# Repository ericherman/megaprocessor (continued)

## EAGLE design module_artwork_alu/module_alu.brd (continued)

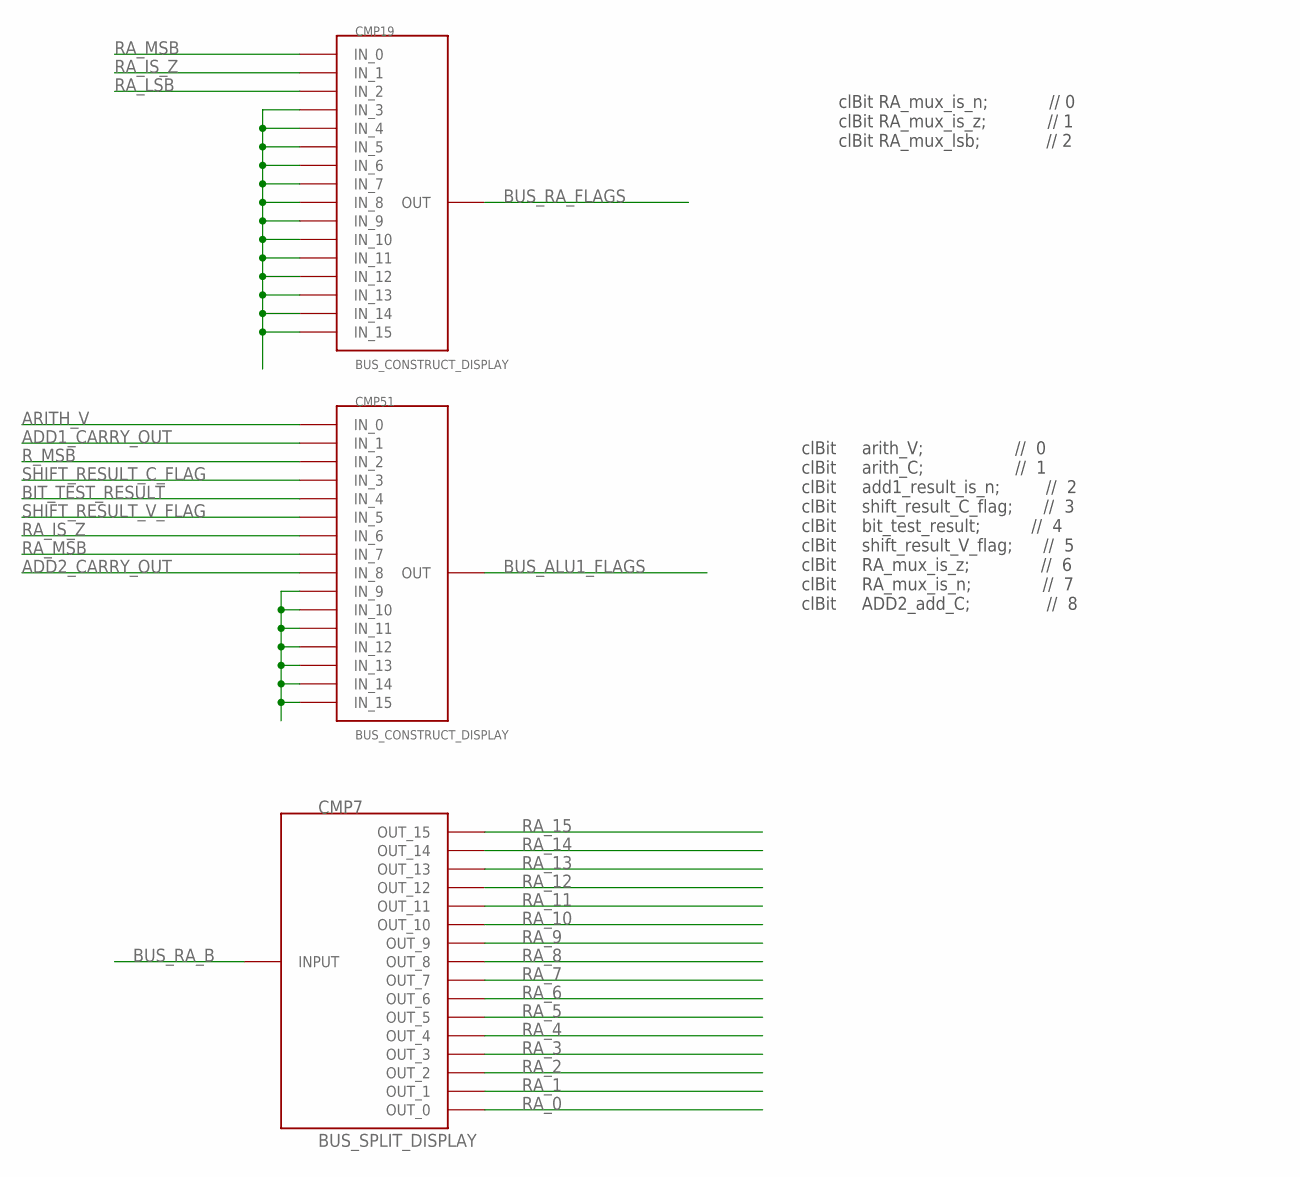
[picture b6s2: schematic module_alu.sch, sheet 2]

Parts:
CMP7: BUS_SPLIT_DISPLAY
CMP19, CMP51: BUS_CONSTRUCT_DISPLAY; BUS_SPLIT_DISPLAY

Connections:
ADD1_CARRY_OUT: CMP51.P$2 (IN_1); also elsewhere on the board
ADD2_CARRY_OUT: CMP51.P$9 (IN_8); also elsewhere on the board
ARITH_V: CMP51.P$1 (IN_0); also elsewhere on the board
BIT_TEST_RESULT: CMP51.P$5 (IN_4); also elsewhere on the board
BUS_ALU1_FLAGS: CMP51.INPUT (OUT)
BUS_RA_B: CMP7.INPUT; also elsewhere on the board
BUS_RA_FLAGS: CMP19.INPUT (OUT)
unnamed: CMP19.P$4 (IN_3), CMP19.P$5 (IN_4), CMP19.P$6 (IN_5), CMP19.P$7 (IN_6), CMP19.P$8 (IN_7), CMP19.P$9 (IN_8), CMP19.P$10 (IN_9), CMP19.P$11 (IN_10), CMP19.P$12 (IN_11), CMP19.P$13 (IN_12), CMP19.P$14 (IN_13), CMP19.P$15 (IN_14), CMP19.P$16 (IN_15)
unnamed: CMP51.P$10 (IN_9), CMP51.P$11 (IN_10), CMP51.P$12 (IN_11), CMP51.P$13 (IN_12), CMP51.P$14 (IN_13), CMP51.P$15 (IN_14), CMP51.P$16 (IN_15)
RA_0: CMP7.P$1 (OUT_0); also elsewhere on the board
RA_1: CMP7.P$2 (OUT_1); also elsewhere on the board
RA_2: CMP7.P$3 (OUT_2); also elsewhere on the board
RA_3: CMP7.P$4 (OUT_3); also elsewhere on the board
RA_4: CMP7.P$5 (OUT_4); also elsewhere on the board
RA_5: CMP7.P$6 (OUT_5); also elsewhere on the board
RA_6: CMP7.P$7 (OUT_6); also elsewhere on the board
RA_7: CMP7.P$8 (OUT_7); also elsewhere on the board
RA_8: CMP7.P$9 (OUT_8); also elsewhere on the board
RA_9: CMP7.P$10 (OUT_9); also elsewhere on the board
RA_10: CMP7.P$11 (OUT_10); also elsewhere on the board
RA_11: CMP7.P$12 (OUT_11); also elsewhere on the board
RA_12: CMP7.P$13 (OUT_12); also elsewhere on the board
RA_13: CMP7.P$14 (OUT_13); also elsewhere on the board
RA_14: CMP7.P$15 (OUT_14); also elsewhere on the board
RA_15: CMP7.P$16 (OUT_15); also elsewhere on the board
RA_IS_Z: CMP19.P$2 (IN_1), CMP51.P$7 (IN_6); also elsewhere on the board
RA_LSB: CMP19.P$3 (IN_2); also elsewhere on the board
RA_MSB: CMP19.P$1 (IN_0), CMP51.P$8 (IN_7); also elsewhere on the board
R_MSB: CMP51.P$3 (IN_2); also elsewhere on the board
SHIFT_RESULT_C_FLAG: CMP51.P$4 (IN_3); also elsewhere on the board
SHIFT_RESULT_V_FLAG: CMP51.P$6 (IN_5); also elsewhere on the board

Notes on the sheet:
clBit RA_mux_is_n; // 0 clBit RA_mux_is_z; // 1 clBit RA_mux_lsb; // 2
clBit arith_V; // 0 clBit arith_C; // 1 clBit add1_result_is_n; // 2 clBit shift_result_C_flag; // 3 clBit bit_test_result; // 4 clBit shift_result_V_flag; // 5 clBit RA_mux_is_z; // 6 clBit RA_mux_is_n; // 7 clBit ADD2_add_C; // 8

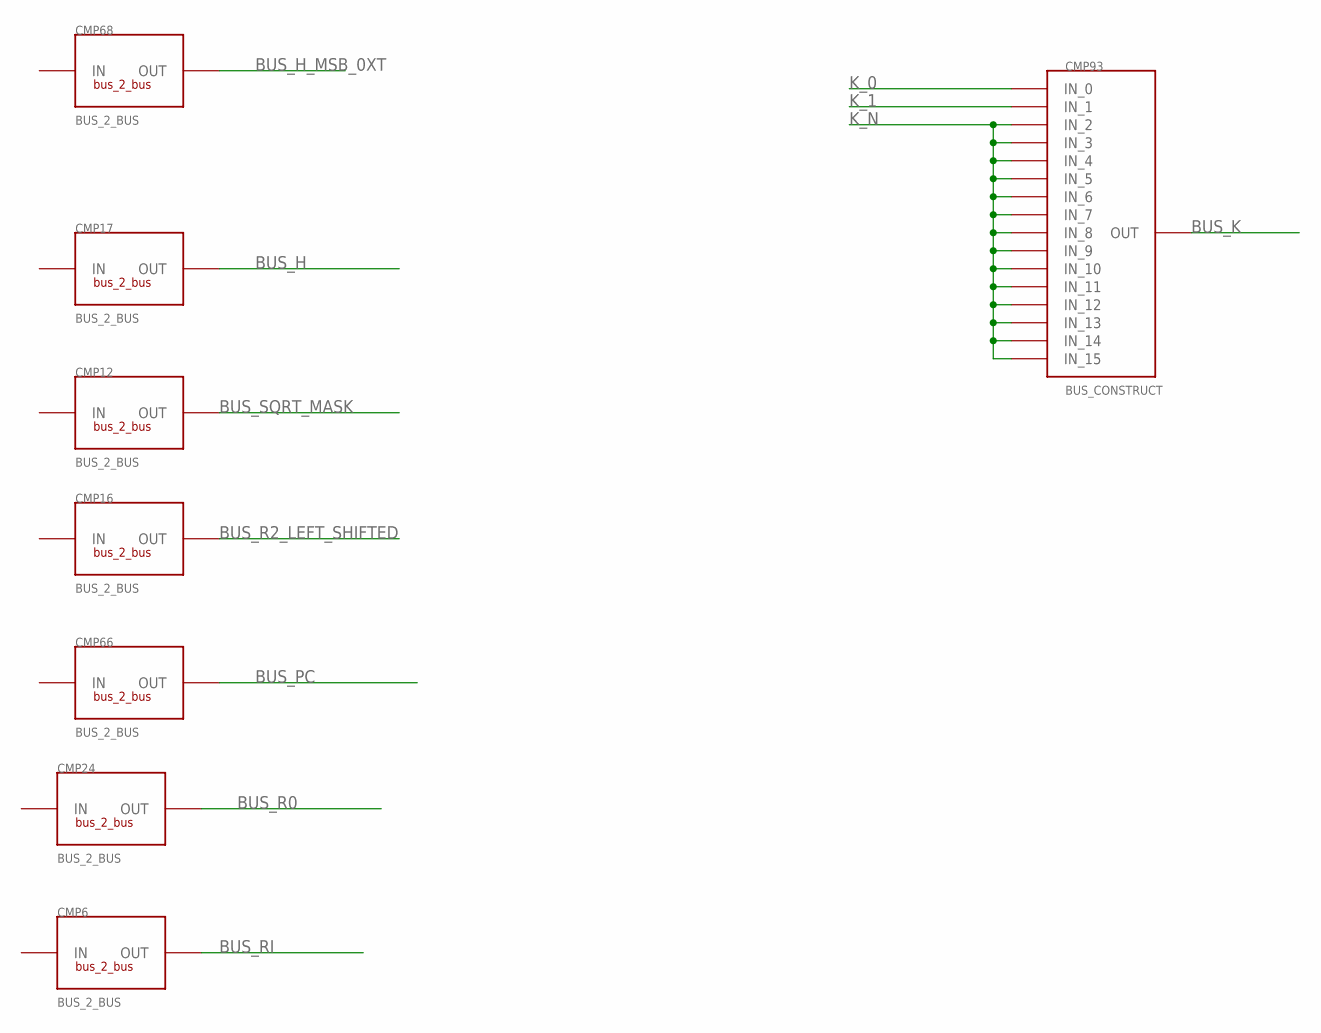
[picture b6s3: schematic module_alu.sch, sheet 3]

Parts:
CMP6, CMP12, CMP16, CMP17, CMP24, CMP66, CMP68: BUS_2_BUS; BUS2BUS
CMP93: BUS_CONSTRUCT; BUS_SPLIT

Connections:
BUS_H: CMP17.P$2 (OUT); also elsewhere on the board
BUS_H_MSB_0XT: CMP68.P$2 (OUT); also elsewhere on the board
BUS_K: CMP93.INPUT (OUT); also elsewhere on the board
BUS_PC: CMP66.P$2 (OUT); also elsewhere on the board
BUS_R0: CMP24.P$2 (OUT); also elsewhere on the board
BUS_R2_LEFT_SHIFTED: CMP16.P$2 (OUT); also elsewhere on the board
BUS_RI: CMP6.P$2 (OUT); also elsewhere on the board
BUS_SQRT_MASK: CMP12.P$2 (OUT); also elsewhere on the board
K_0: CMP93.P$1 (IN_0); also elsewhere on the board
K_1: CMP93.P$2 (IN_1); also elsewhere on the board
K_N: CMP93.P$3 (IN_2), CMP93.P$4 (IN_3), CMP93.P$5 (IN_4), CMP93.P$6 (IN_5), CMP93.P$7 (IN_6), CMP93.P$8 (IN_7), CMP93.P$9 (IN_8), CMP93.P$10 (IN_9), CMP93.P$11 (IN_10), CMP93.P$12 (IN_11), CMP93.P$13 (IN_12), CMP93.P$14 (IN_13), CMP93.P$15 (IN_14), CMP93.P$16 (IN_15); also elsewhere on the board

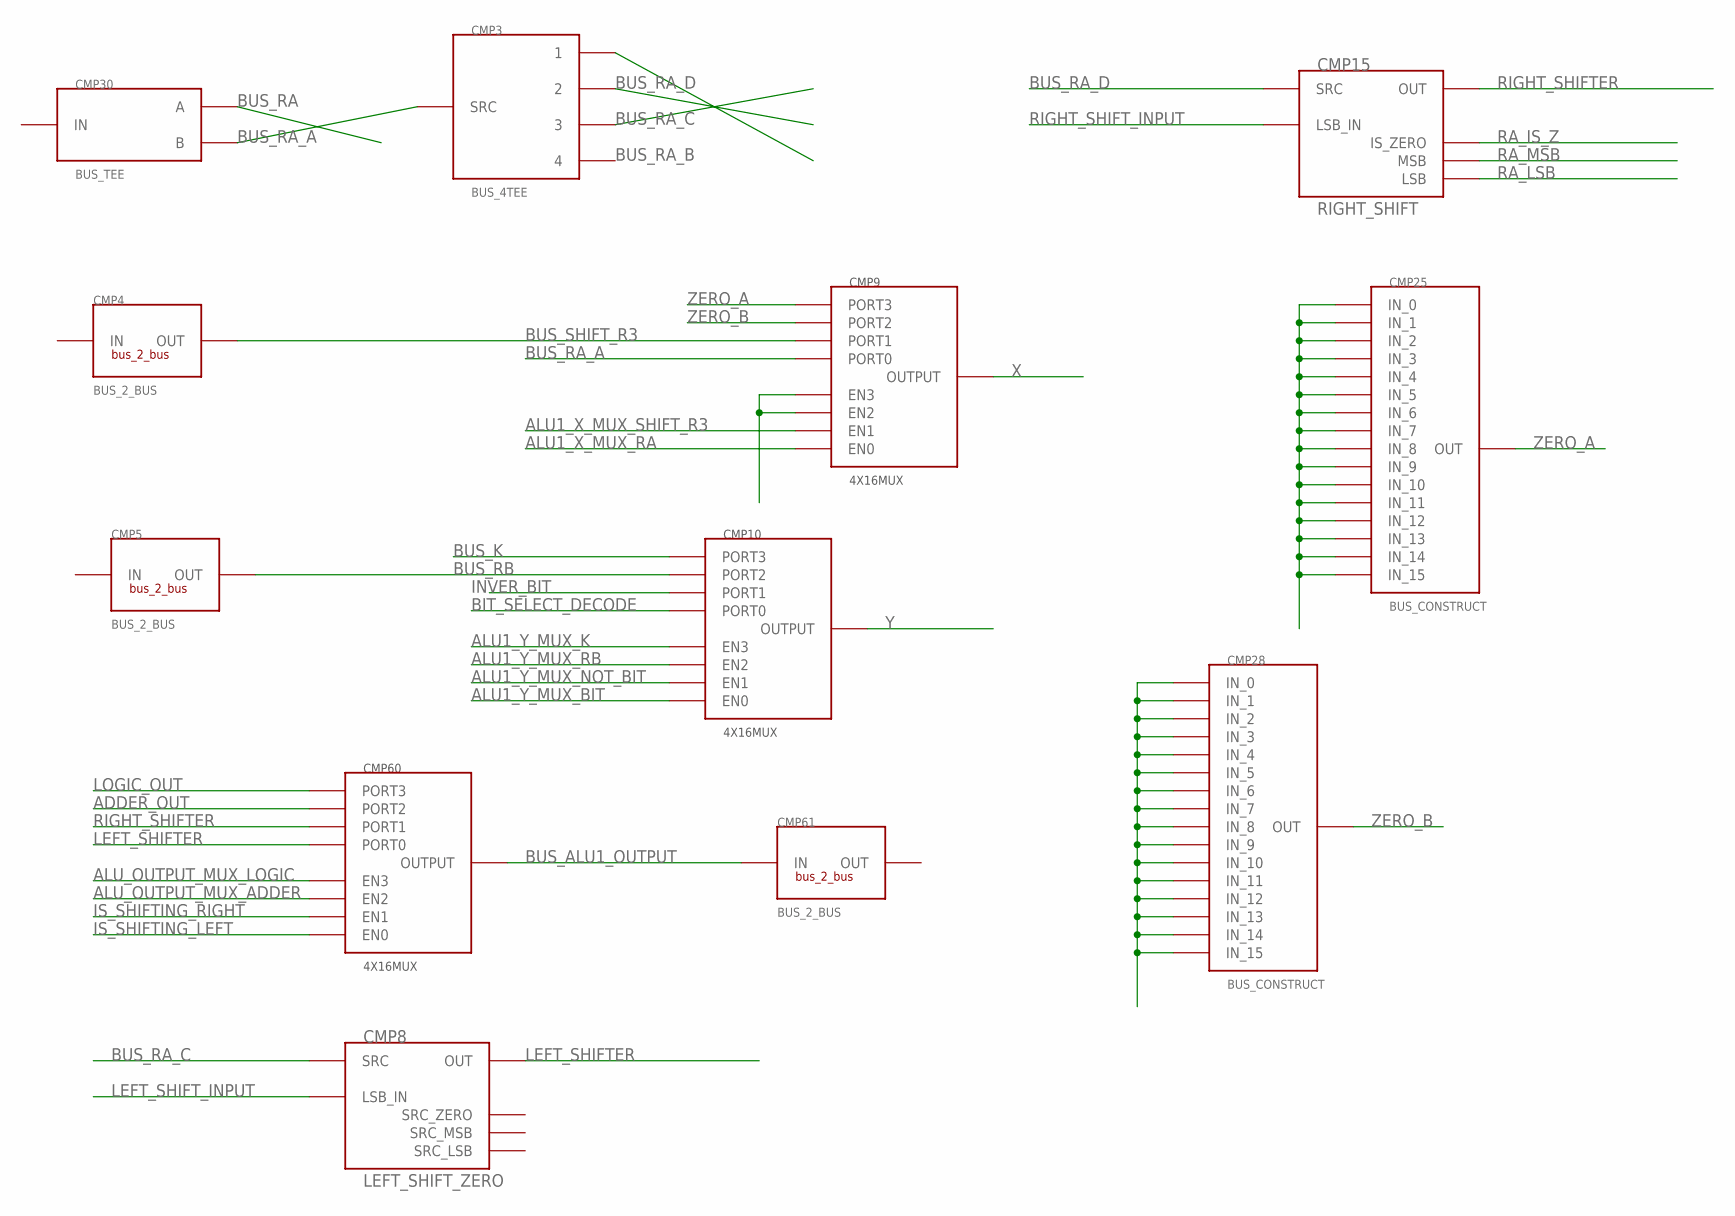
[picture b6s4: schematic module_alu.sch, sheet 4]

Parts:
CMP3: BUS_4TEE
CMP4, CMP5, CMP61: BUS_2_BUS; BUS2BUS
CMP8: LEFT_SHIFT_ZERO; SHIFT_ZERO
CMP9, CMP10, CMP60: 4X16MUX
CMP15: RIGHT_SHIFT; SHIFT_ZERO
CMP25, CMP28: BUS_CONSTRUCT; BUS_SPLIT
CMP30: BUS_TEE

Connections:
ADDER_OUT: CMP60.PORT2; also elsewhere on the board
ALU1_X_MUX_RA: CMP9.EN0; also elsewhere on the board
ALU1_X_MUX_SHIFT_R3: CMP9.EN1; also elsewhere on the board
ALU1_Y_MUX_BIT: CMP10.EN0; also elsewhere on the board
ALU1_Y_MUX_K: CMP10.EN3; also elsewhere on the board
ALU1_Y_MUX_NOT_BIT: CMP10.EN1; also elsewhere on the board
ALU1_Y_MUX_RB: CMP10.EN2; also elsewhere on the board
ALU_OUTPUT_MUX_ADDER: CMP60.EN2; also elsewhere on the board
ALU_OUTPUT_MUX_LOGIC: CMP60.EN3; also elsewhere on the board
BIT_SELECT_DECODE: CMP10.PORT0; also elsewhere on the board
BUS_ALU1_OUTPUT: CMP60.PORTOUT (OUTPUT), CMP61.P$1 (IN)
BUS_K: CMP10.PORT3; also elsewhere on the board
BUS_RA: CMP3.SRC, CMP30.OUTB (B)
BUS_RA_A: CMP9.PORT0, CMP30.OUT_A (A)
BUS_RA_B: CMP3.1; also elsewhere on the board
BUS_RA_C: CMP3.2, CMP8.LSRC (SRC)
BUS_RA_D: CMP3.3, CMP15.RSRC (SRC)
BUS_RB: CMP5.P$2 (OUT), CMP10.PORT2
BUS_SHIFT_R3: CMP4.P$2 (OUT), CMP9.PORT1
INVER_BIT: CMP10.PORT1; also elsewhere on the board
IS_SHIFTING_LEFT: CMP60.EN0; also elsewhere on the board
IS_SHIFTING_RIGHT: CMP60.EN1; also elsewhere on the board
LEFT_SHIFTER: CMP8.RSRC (OUT), CMP60.PORT0
LEFT_SHIFT_INPUT: CMP8.SHIFT_IN (LSB_IN); also elsewhere on the board
LOGIC_OUT: CMP60.PORT3; also elsewhere on the board
unnamed: CMP9.EN2, CMP9.EN3
unnamed: CMP25.P$1 (IN_0), CMP25.P$2 (IN_1), CMP25.P$3 (IN_2), CMP25.P$4 (IN_3), CMP25.P$5 (IN_4), CMP25.P$6 (IN_5), CMP25.P$7 (IN_6), CMP25.P$8 (IN_7), CMP25.P$9 (IN_8), CMP25.P$10 (IN_9), CMP25.P$11 (IN_10), CMP25.P$12 (IN_11), CMP25.P$13 (IN_12), CMP25.P$14 (IN_13), CMP25.P$15 (IN_14), CMP25.P$16 (IN_15)
unnamed: CMP28.P$1 (IN_0), CMP28.P$2 (IN_1), CMP28.P$3 (IN_2), CMP28.P$4 (IN_3), CMP28.P$5 (IN_4), CMP28.P$6 (IN_5), CMP28.P$7 (IN_6), CMP28.P$8 (IN_7), CMP28.P$9 (IN_8), CMP28.P$10 (IN_9), CMP28.P$11 (IN_10), CMP28.P$12 (IN_11), CMP28.P$13 (IN_12), CMP28.P$14 (IN_13), CMP28.P$15 (IN_14), CMP28.P$16 (IN_15)
RA_IS_Z: CMP15.IS_ZERO; also elsewhere on the board
RA_LSB: CMP15.LSB; also elsewhere on the board
RA_MSB: CMP15.MSB; also elsewhere on the board
RIGHT_SHIFTER: CMP15.LSRC (OUT), CMP60.PORT1
RIGHT_SHIFT_INPUT: CMP15.SHIFT_IN (LSB_IN); also elsewhere on the board
X: CMP9.PORTOUT (OUTPUT); also elsewhere on the board
Y: CMP10.PORTOUT (OUTPUT); also elsewhere on the board
ZERO_A: CMP9.PORT3, CMP25.INPUT (OUT)
ZERO_B: CMP9.PORT2, CMP28.INPUT (OUT)

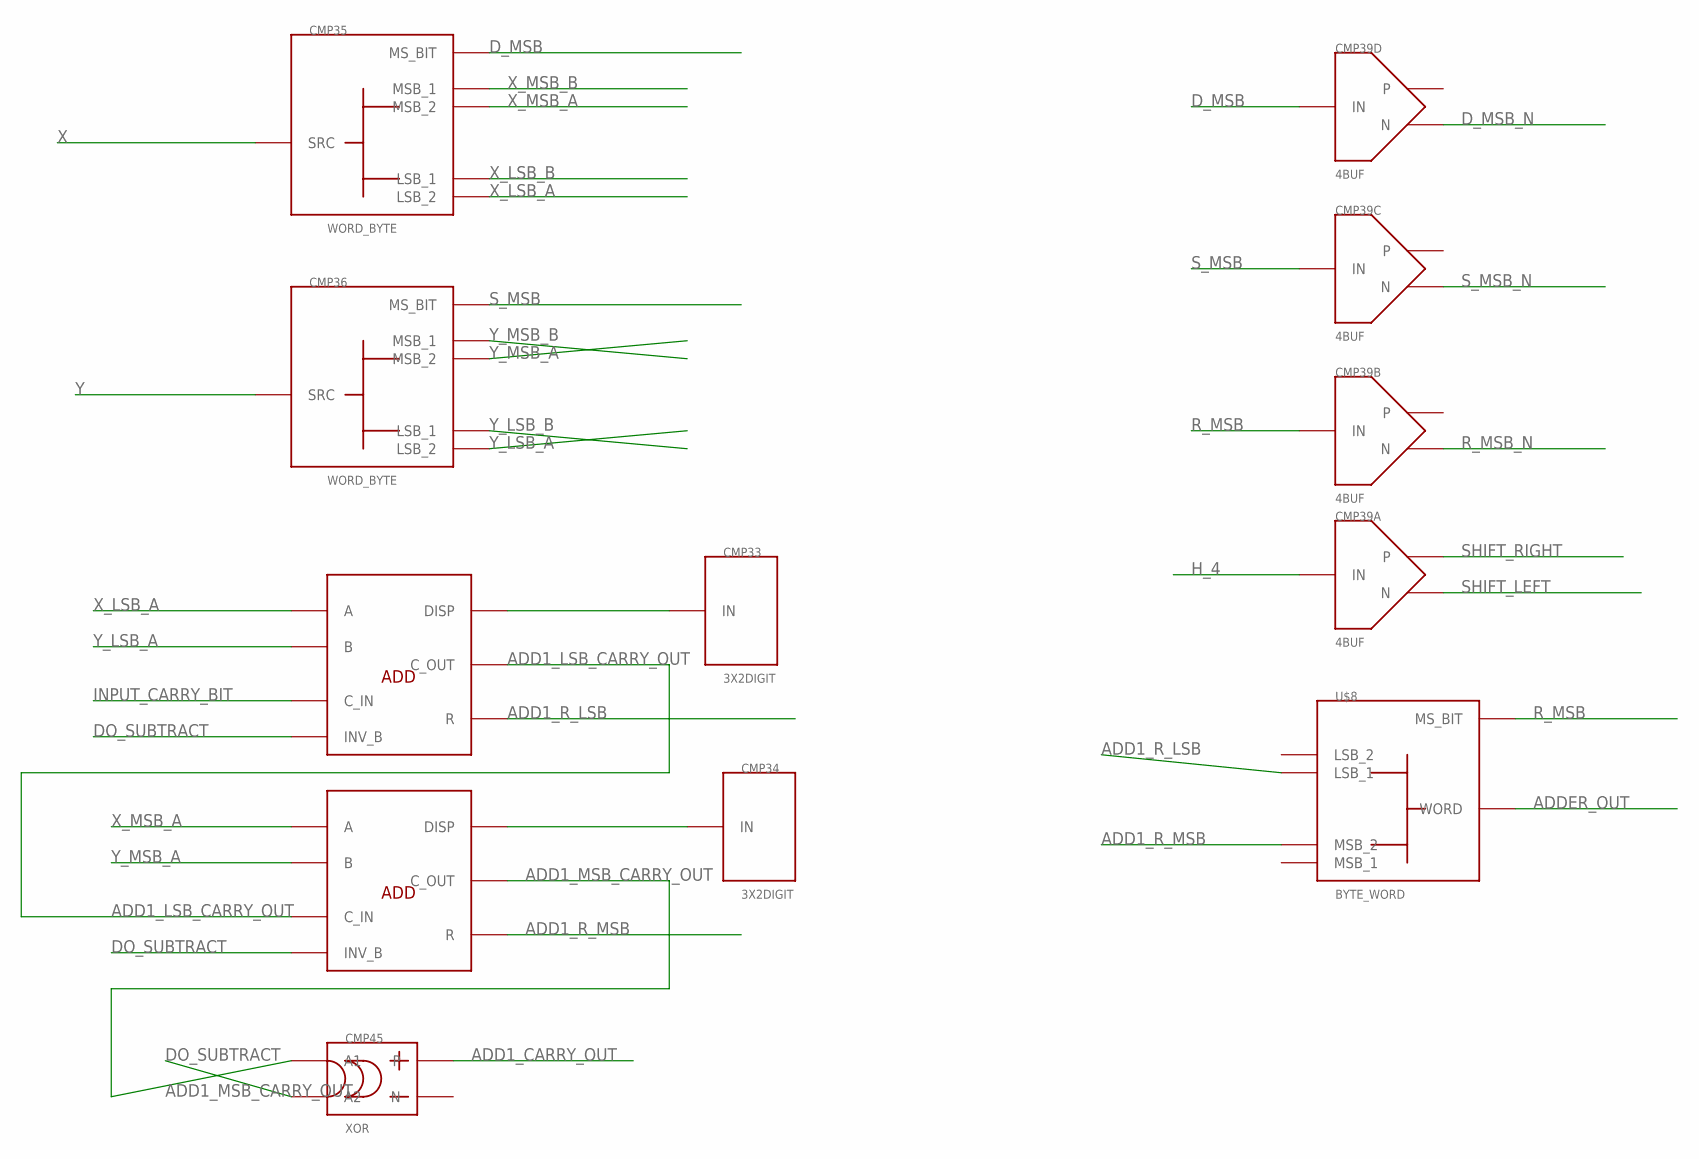
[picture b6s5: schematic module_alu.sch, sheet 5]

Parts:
CMP31, CMP32: 8BIT_ADD_SUB
CMP33, CMP34: 3X2DIGIT
CMP35, CMP36: WORD_BYTE
CMP39: 4BUF
CMP45: XOR
U$8: BYTE_WORD; WORD_BYTE

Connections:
ADD1_CARRY_OUT: CMP45.OUT_P; also elsewhere on the board
ADD1_LSB_CARRY_OUT: CMP31.C_OUT, CMP32.C_IN
ADD1_MSB_CARRY_OUT: CMP32.C_OUT, CMP45.P$1 (A1)
ADD1_R_LSB: CMP31.R, U$8.LSB_1
ADD1_R_MSB: CMP32.R, U$8.MSB_2
ADDER_OUT: U$8.SRC (WORD); also elsewhere on the board
DO_SUBTRACT: CMP31.INV_B, CMP32.INV_B, CMP45.P$2 (A2); also elsewhere on the board
D_MSB: CMP35.MS_BIT, CMP39.A4 (IN); also elsewhere on the board
D_MSB_N: CMP39.N4 (N); also elsewhere on the board
H_4: CMP39.A1 (IN); also elsewhere on the board
INPUT_CARRY_BIT: CMP31.C_IN; also elsewhere on the board
unnamed: CMP31.DISP, CMP33.P$1
unnamed: CMP32.DISP, CMP34.P$1
R_MSB: CMP39.A2 (IN), U$8.MS_BIT; also elsewhere on the board
R_MSB_N: CMP39.N2 (N); also elsewhere on the board
SHIFT_LEFT: CMP39.N1 (N); also elsewhere on the board
SHIFT_RIGHT: CMP39.P1; also elsewhere on the board
S_MSB: CMP36.MS_BIT, CMP39.A3 (IN); also elsewhere on the board
S_MSB_N: CMP39.N3 (N); also elsewhere on the board
X: CMP35.SRC; also elsewhere on the board
X_LSB_A: CMP31.A, CMP35.LSB_2
X_LSB_B: CMP35.LSB_1; also elsewhere on the board
X_MSB_A: CMP32.A, CMP35.MSB_2
X_MSB_B: CMP35.MSB_1; also elsewhere on the board
Y: CMP36.SRC; also elsewhere on the board
Y_LSB_A: CMP31.B, CMP36.LSB_1
Y_LSB_B: CMP36.LSB_2; also elsewhere on the board
Y_MSB_A: CMP32.B, CMP36.MSB_1
Y_MSB_B: CMP36.MSB_2; also elsewhere on the board

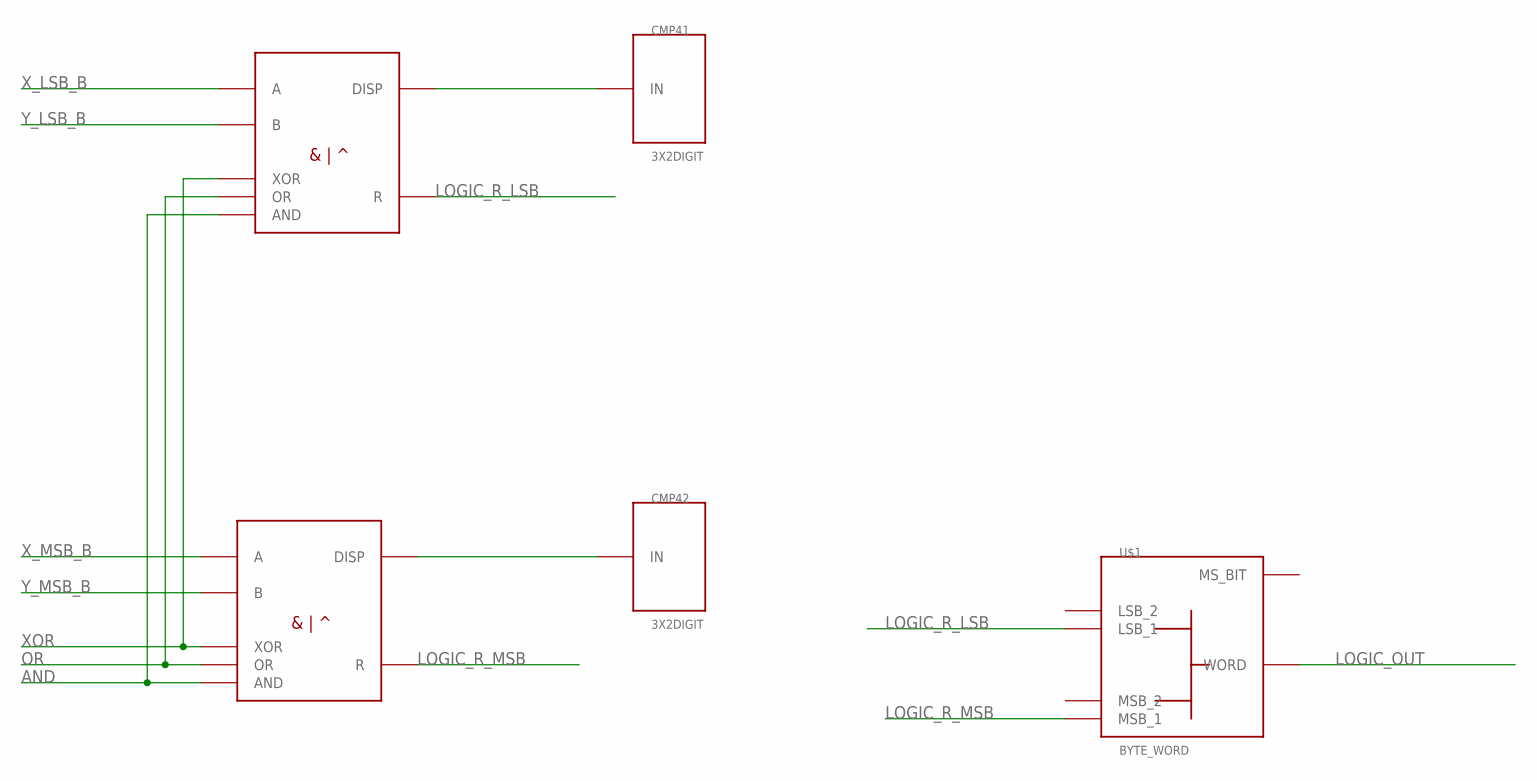
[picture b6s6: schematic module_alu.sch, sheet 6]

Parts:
CMP41, CMP42: 3X2DIGIT
CMP46, CMP47: 8BIT_LOGIC
U$1: BYTE_WORD; WORD_BYTE

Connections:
AND: CMP46.AND, CMP47.AND; also elsewhere on the board
LOGIC_OUT: U$1.SRC (WORD); also elsewhere on the board
LOGIC_R_LSB: CMP47.R, U$1.LSB_1
LOGIC_R_MSB: CMP46.R, U$1.MSB_1
unnamed: CMP41.P$1, CMP47.DISP
unnamed: CMP42.P$1, CMP46.DISP
OR: CMP46.OR, CMP47.OR; also elsewhere on the board
XOR: CMP46.XOR, CMP47.XOR; also elsewhere on the board
X_LSB_B: CMP47.A; also elsewhere on the board
X_MSB_B: CMP46.A; also elsewhere on the board
Y_LSB_B: CMP47.B; also elsewhere on the board
Y_MSB_B: CMP46.B; also elsewhere on the board

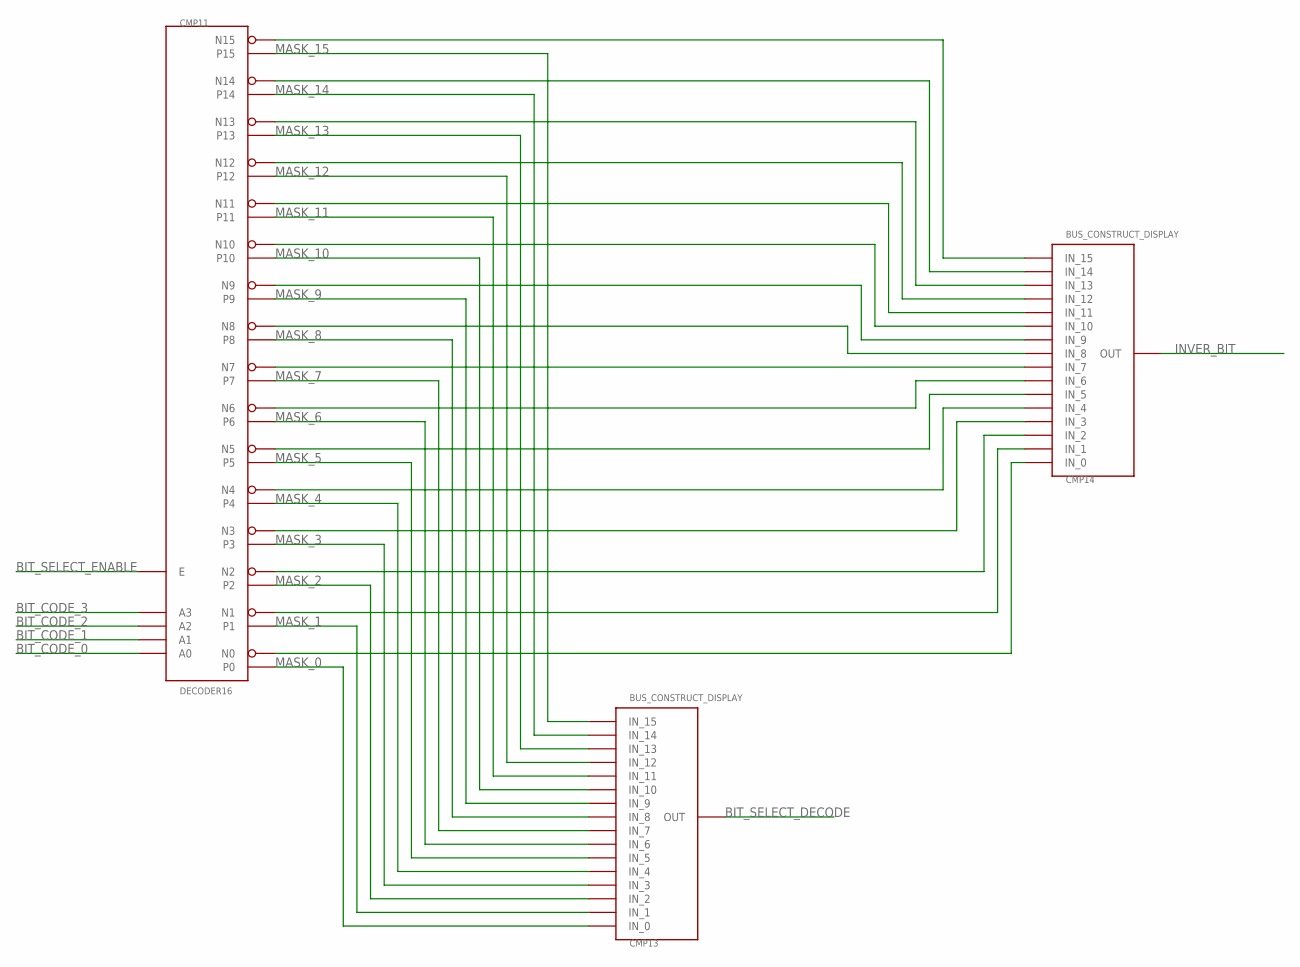
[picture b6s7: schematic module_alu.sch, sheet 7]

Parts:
CMP11: DECODER16
CMP13, CMP14: BUS_CONSTRUCT_DISPLAY; BUS_SPLIT_DISPLAY

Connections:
BIT_CODE_0: CMP11.A0; also elsewhere on the board
BIT_CODE_1: CMP11.A1; also elsewhere on the board
BIT_CODE_2: CMP11.A2; also elsewhere on the board
BIT_CODE_3: CMP11.A3; also elsewhere on the board
BIT_SELECT_DECODE: CMP13.INPUT (OUT); also elsewhere on the board
BIT_SELECT_ENABLE: CMP11.E; also elsewhere on the board
INVER_BIT: CMP14.INPUT (OUT); also elsewhere on the board
MASK_0: CMP11.P0, CMP13.P$1 (IN_0); also elsewhere on the board
MASK_1: CMP11.P1, CMP13.P$2 (IN_1); also elsewhere on the board
MASK_2: CMP11.P2, CMP13.P$3 (IN_2); also elsewhere on the board
MASK_3: CMP11.P3, CMP13.P$4 (IN_3); also elsewhere on the board
MASK_4: CMP11.P4, CMP13.P$5 (IN_4); also elsewhere on the board
MASK_5: CMP11.P5, CMP13.P$6 (IN_5); also elsewhere on the board
MASK_6: CMP11.P6, CMP13.P$7 (IN_6); also elsewhere on the board
MASK_7: CMP11.P7, CMP13.P$8 (IN_7); also elsewhere on the board
MASK_8: CMP11.P8, CMP13.P$9 (IN_8); also elsewhere on the board
MASK_9: CMP11.P9, CMP13.P$10 (IN_9); also elsewhere on the board
MASK_10: CMP11.P10, CMP13.P$11 (IN_10); also elsewhere on the board
MASK_11: CMP11.P11, CMP13.P$12 (IN_11); also elsewhere on the board
MASK_12: CMP11.P12, CMP13.P$13 (IN_12); also elsewhere on the board
MASK_13: CMP11.P13, CMP13.P$14 (IN_13); also elsewhere on the board
MASK_14: CMP11.P14, CMP13.P$15 (IN_14); also elsewhere on the board
MASK_15: CMP11.P15, CMP13.P$16 (IN_15); also elsewhere on the board
unnamed: CMP11.N0, CMP14.P$1 (IN_0)
unnamed: CMP11.N1, CMP14.P$2 (IN_1)
unnamed: CMP11.N2, CMP14.P$3 (IN_2)
unnamed: CMP11.N3, CMP14.P$4 (IN_3)
unnamed: CMP11.N4, CMP14.P$5 (IN_4)
unnamed: CMP11.N5, CMP14.P$6 (IN_5)
unnamed: CMP11.N6, CMP14.P$7 (IN_6)
unnamed: CMP11.N7, CMP14.P$8 (IN_7)
unnamed: CMP11.N8, CMP14.P$9 (IN_8)
unnamed: CMP11.N9, CMP14.P$10 (IN_9)
unnamed: CMP11.N10, CMP14.P$11 (IN_10)
unnamed: CMP11.N11, CMP14.P$12 (IN_11)
unnamed: CMP11.N12, CMP14.P$13 (IN_12)
unnamed: CMP11.N13, CMP14.P$14 (IN_13)
unnamed: CMP11.N14, CMP14.P$15 (IN_14)
unnamed: CMP11.N15, CMP14.P$16 (IN_15)

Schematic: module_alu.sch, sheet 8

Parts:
CMP48, CMP49: 2X3AND_OR
CMP50: 2AND
CMP52: 4X2AND_OR

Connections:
ARITH_ADD_V: CMP48.OUT_P, CMP52.P$8 (D1)
ARITH_NEG_V: CMP50.OUT_P, CMP52.P$4 (B1)
ARITH_SUB_V: CMP49.OUT_P, CMP52.P$6 (C1)
ARITH_V: CMP52.OUT_P; also elsewhere on the board
D_MSB: CMP48.P$4 (B0), CMP49.P$5 (B1); also elsewhere on the board
D_MSB_N: CMP48.P$3 (A2), CMP49.P$1 (A0); also elsewhere on the board
unnamed: CMP52.P$1 (A0), CMP52.P$2 (A1)
R_MSB: CMP48.P$2 (A1), CMP49.P$3 (A2), CMP50.P$2 (2); also elsewhere on the board
R_MSB_N: CMP48.P$5 (B1), CMP49.P$4 (B0); also elsewhere on the board
S_MSB: CMP48.P$6 (B2), CMP49.P$2 (A1), CMP50.P$1 (1); also elsewhere on the board
S_MSB_N: CMP48.P$1 (A0), CMP49.P$6 (B2); also elsewhere on the board
USE_ADD_V: CMP52.P$7 (D0); also elsewhere on the board
USE_NEG_V: CMP52.P$3 (B0); also elsewhere on the board
USE_SUB_V: CMP52.P$5 (C0); also elsewhere on the board

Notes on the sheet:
arith_add_V = Cpnt_2x3AND_OR( S_msb, D_msb, ~R_msb, ~S_msb, ~D_msb, R_msb);
arith_sub_V = Cpnt_2x3AND_OR(~S_msb, D_msb, ~R_msb, S_msb, ~D_msb, R_msb);
arith_neg_V = Cpnt_2AND(S_msb, R_msb);
arith_V = Cpnt_4x2AND_OR(arith_add_V,bus_alu1_operation_ctrl.use_add_V, arith_sub_V,bus_alu1_operation_ctrl.use_sub_V, arith_neg_V,bus_alu1_operation_ctrl.use_neg_V, BIT_VAL_0, BIT_VAL_0);

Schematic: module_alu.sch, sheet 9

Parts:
CMP53, CMP54: 8X2AND_OR
CMP55: 2OR

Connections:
BIT_TEST_RESULT: CMP55.OUT_M (N); also elsewhere on the board
MASK_0: CMP54.P$2 (A1); also elsewhere on the board
MASK_1: CMP54.P$4 (B1); also elsewhere on the board
MASK_2: CMP54.P$6 (C1); also elsewhere on the board
MASK_3: CMP54.P$8 (D1); also elsewhere on the board
MASK_4: CMP54.P$10 (E2); also elsewhere on the board
MASK_5: CMP54.P$12 (F2); also elsewhere on the board
MASK_6: CMP54.P$14 (G2); also elsewhere on the board
MASK_7: CMP54.P$16 (H2); also elsewhere on the board
MASK_8: CMP53.P$2 (A1); also elsewhere on the board
MASK_9: CMP53.P$4 (B1); also elsewhere on the board
MASK_10: CMP53.P$6 (C1); also elsewhere on the board
MASK_11: CMP53.P$8 (D1); also elsewhere on the board
MASK_12: CMP53.P$10 (E2); also elsewhere on the board
MASK_13: CMP53.P$12 (F2); also elsewhere on the board
MASK_14: CMP53.P$14 (G2); also elsewhere on the board
MASK_15: CMP53.P$16 (H2); also elsewhere on the board
unnamed: CMP53.OUT_P, CMP55.P$2 (A1)
unnamed: CMP54.OUT_P, CMP55.P$1 (A2)
RA_0: CMP54.P$1 (A0); also elsewhere on the board
RA_1: CMP54.P$3 (B0); also elsewhere on the board
RA_2: CMP54.P$5 (C0); also elsewhere on the board
RA_3: CMP54.P$7 (D0); also elsewhere on the board
RA_4: CMP54.P$9 (E1); also elsewhere on the board
RA_5: CMP54.P$11 (F1); also elsewhere on the board
RA_6: CMP54.P$13 (G1); also elsewhere on the board
RA_7: CMP54.P$15 (H1); also elsewhere on the board
RA_8: CMP53.P$1 (A0); also elsewhere on the board
RA_9: CMP53.P$3 (B0); also elsewhere on the board
RA_10: CMP53.P$5 (C0); also elsewhere on the board
RA_11: CMP53.P$7 (D0); also elsewhere on the board
RA_12: CMP53.P$9 (E1); also elsewhere on the board
RA_13: CMP53.P$11 (F1); also elsewhere on the board
RA_14: CMP53.P$13 (G1); also elsewhere on the board
RA_15: CMP53.P$15 (H1); also elsewhere on the board

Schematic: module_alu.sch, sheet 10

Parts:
CMP38: XOR
CMP56: 2X2AND_OR

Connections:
RA_14: CMP38.P$2 (A2); also elsewhere on the board
RA_LSB: CMP56.P$1 (A0); also elsewhere on the board
RA_MSB: CMP38.P$1 (A1), CMP56.P$3 (B0); also elsewhere on the board
SHIFT_LEFT: CMP56.P$4 (B1); also elsewhere on the board
SHIFT_RESULT_C_FLAG: CMP56.OUT_P; also elsewhere on the board
SHIFT_RESULT_V_FLAG: CMP38.OUT_P; also elsewhere on the board
SHIFT_RIGHT: CMP56.P$2 (A1); also elsewhere on the board

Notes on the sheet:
shift_result_C_flag = Cpnt_2x2AND_OR(~bus_alu1_operation_ctrl.H_4, bus_RA[15], bus_alu1_operation_ctrl.H_4, bus_RA[ 0]);
shift_result_V_flag = Cpnt_XOR( bus_RA[15], bus_RA[14] );

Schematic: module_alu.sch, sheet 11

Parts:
CMP70, CMP71: 4X16MUX
CMP72: BUS_CONSTRUCT; BUS_SPLIT

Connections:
ADD2_X: CMP70.PORTOUT (OUTPUT); also elsewhere on the board
ADD2_X_MUX_PC: CMP70.EN1; also elsewhere on the board
ADD2_X_MUX_RI: CMP70.EN3; also elsewhere on the board
ADD2_X_MUX_SHIFT_R2: CMP70.EN2; also elsewhere on the board
ADD2_X_MUX_SQRT_MASK: CMP70.EN0; also elsewhere on the board
ADD2_Y: CMP71.PORTOUT (OUTPUT); also elsewhere on the board
ADD2_Y_MUX_H: CMP71.EN2; also elsewhere on the board
ADD2_Y_MUX_P1: CMP71.EN0; also elsewhere on the board
ADD2_Y_MUX_R0: CMP71.EN1; also elsewhere on the board
ADD2_Y_MUX_WEIGHT: CMP71.EN3; also elsewhere on the board
BUS_H: CMP71.PORT2; also elsewhere on the board
BUS_H_MSB_0XT: CMP71.PORT3; also elsewhere on the board
BUS_PC: CMP70.PORT1; also elsewhere on the board
BUS_R0: CMP71.PORT1; also elsewhere on the board
BUS_R2_LEFT_SHIFTED: CMP70.PORT2; also elsewhere on the board
BUS_RI: CMP70.PORT3; also elsewhere on the board
BUS_SQRT_MASK: CMP70.PORT0; also elsewhere on the board
unnamed: CMP72.P$2 (IN_1), CMP72.P$3 (IN_2), CMP72.P$4 (IN_3), CMP72.P$5 (IN_4), CMP72.P$6 (IN_5), CMP72.P$7 (IN_6), CMP72.P$8 (IN_7), CMP72.P$9 (IN_8), CMP72.P$10 (IN_9), CMP72.P$11 (IN_10), CMP72.P$12 (IN_11), CMP72.P$13 (IN_12), CMP72.P$14 (IN_13), CMP72.P$15 (IN_14), CMP72.P$16 (IN_15)
PLUS_1: CMP71.PORT0, CMP72.INPUT (OUT)

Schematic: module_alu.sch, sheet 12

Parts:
CMP18: XOR
CMP26, CMP27: WORD_BYTE
CMP82, CMP83: 8BIT_ADD_SUB
CMP84, CMP85: 3X2DIGIT
U$3: BYTE_WORD; WORD_BYTE

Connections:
ADD2_CARRY_IN: CMP82.C_IN; also elsewhere on the board
ADD2_CARRY_OUT: CMP18.OUT_P; also elsewhere on the board
ADD2_DO_SUBTRACT: CMP18.P$1 (A1), CMP82.INV_B, CMP83.INV_B; also elsewhere on the board
ADD2_D_MSB: CMP26.MS_BIT
ADD2_LSB: CMP82.R, U$3.LSB_2
ADD2_LSB_CARRY_OUT: CMP82.C_OUT, CMP83.C_IN
ADD2_MSB: CMP83.R, U$3.MSB_2
ADD2_MSB_CARRY_OUT: CMP18.P$2 (A2), CMP83.C_OUT
ADD2_S_MSB: CMP27.MS_BIT
ADD2_X: CMP26.SRC; also elsewhere on the board
ADD2_X_LSB: CMP26.LSB_1, CMP82.A
ADD2_X_MSB: CMP26.MSB_1, CMP83.A
ADD2_Y: CMP27.SRC; also elsewhere on the board
ADD2_Y_LSB: CMP27.LSB_1, CMP82.B
ADD2_Y_MSB: CMP27.MSB_1, CMP83.B
unnamed: CMP82.DISP, CMP84.P$1
unnamed: CMP83.DISP, CMP85.P$1

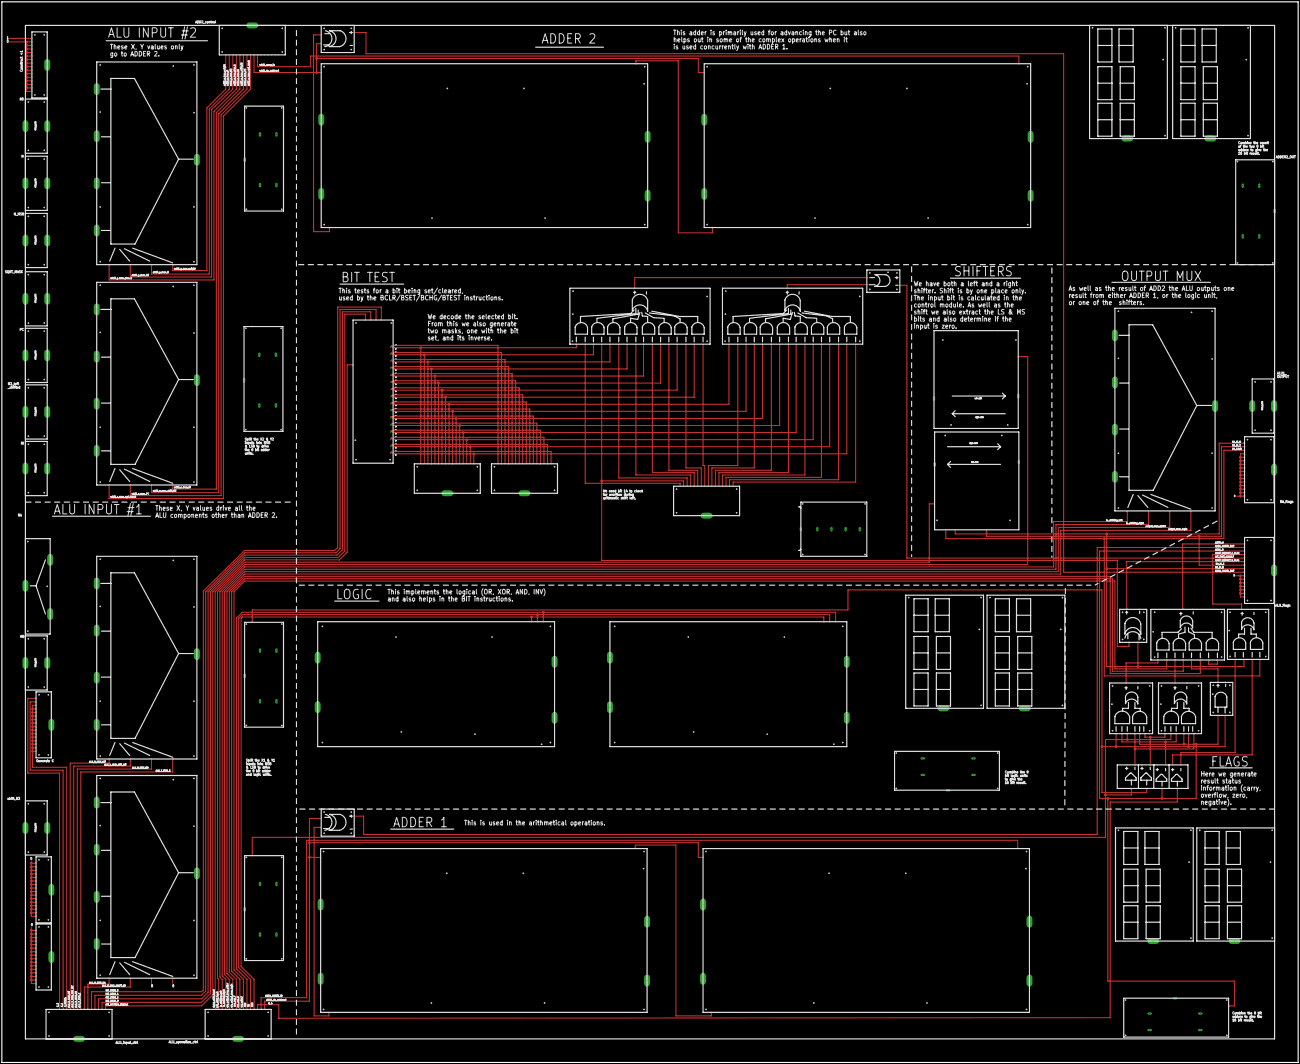
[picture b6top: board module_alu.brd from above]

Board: 2 copper layers, 1397.0 x 1143.0 mm, 63 parts (0 on the bottom side), 173 nets.

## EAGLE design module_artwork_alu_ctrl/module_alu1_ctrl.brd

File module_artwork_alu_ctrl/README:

ALU Control

This module generates the control signals for the ALU module. To do this
it uses information from the decoder modules together with current
state, the current status and the H register (for SHIFT and BIT) to work
out what needs to be done this cycle. It also generates the sequence of
values required for the SQRT algorithm.

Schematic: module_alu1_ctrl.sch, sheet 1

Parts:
CMP13, CMP15, CMP21: BUS_SPLIT_DISPLAY

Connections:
BUS_H_D: CMP13.INPUT
BUS_PS: CMP21.INPUT
BUS_RA_FLAGS: CMP15.INPUT
FLAG_C: CMP21.P$6 (OUT_5)
FLAG_D: CMP21.P$7 (OUT_6)
FLAG_F0: CMP21.P$9 (OUT_8)
FLAG_F1: CMP21.P$10 (OUT_9)
FLAG_F2: CMP21.P$11 (OUT_10)
FLAG_F3: CMP21.P$12 (OUT_11); also elsewhere on the board
FLAG_F4: CMP21.P$13 (OUT_12)
FLAG_F5: CMP21.P$14 (OUT_13)
FLAG_F6: CMP21.P$15 (OUT_14); also elsewhere on the board
FLAG_I: CMP21.P$1 (OUT_0)
FLAG_N: CMP21.P$2 (OUT_1)
FLAG_V: CMP21.P$4 (OUT_3)
FLAG_X: CMP21.P$5 (OUT_4); also elsewhere on the board
FLAG_Z: CMP21.P$3 (OUT_2)
H_0: CMP13.P$1 (OUT_0); also elsewhere on the board
H_1: CMP13.P$2 (OUT_1); also elsewhere on the board
H_2: CMP13.P$3 (OUT_2); also elsewhere on the board
H_3: CMP13.P$4 (OUT_3); also elsewhere on the board
H_4: CMP13.P$5 (OUT_4); also elsewhere on the board
H_5: CMP13.P$6 (OUT_5)
H_6: CMP13.P$7 (OUT_6); also elsewhere on the board
H_7: CMP13.P$8 (OUT_7); also elsewhere on the board
H_8: CMP13.P$9 (OUT_8)
H_9: CMP13.P$10 (OUT_9)
H_10: CMP13.P$11 (OUT_10)
H_11: CMP13.P$12 (OUT_11)
H_12: CMP13.P$13 (OUT_12)
H_13: CMP13.P$14 (OUT_13)
H_14: CMP13.P$15 (OUT_14)
H_15: CMP13.P$16 (OUT_15)
RA_MUX_IS_N: CMP15.P$1 (OUT_0); also elsewhere on the board
RA_MUX_IS_Z: CMP15.P$2 (OUT_1)
RA_MUX_LSB: CMP15.P$3 (OUT_2); also elsewhere on the board

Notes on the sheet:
clBit RA_mux_is_n; // 0 clBit RA_mux_is_z; // 1 clBit RA_mux_lsb; // 2

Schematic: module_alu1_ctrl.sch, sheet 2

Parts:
CMP1, CMP12, CMP22: BUS_SPLIT_DISPLAY

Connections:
ADD2_X_MUX_RI__H: CMP22.P$1 (OUT_0); also elsewhere on the board
ADD2_X_MUX_RI__SP: CMP22.P$3 (OUT_2); also elsewhere on the board
ADD2_X_MUX_RI__SP__JSR_ABS: CMP22.P$2 (OUT_1)
ADDER_X_SPECIAL: CMP22.P$5 (OUT_4); also elsewhere on the board
ADDER_Y_SPECIAL: CMP22.P$6 (OUT_5); also elsewhere on the board
BUS_RNX_SPECIALS: CMP22.INPUT
BUS_RN_ARITH_FLAGS: CMP1.INPUT
BUS_STATE: CMP12.INPUT
NEXT_ADDR_MUX_RI__SP: CMP22.P$4 (OUT_3)
R0_IS_N: CMP1.P$1 (OUT_0); also elsewhere on the board
R0_IS_Z: CMP1.P$5 (OUT_4)
R1_IS_N: CMP1.P$2 (OUT_1); also elsewhere on the board
R1_IS_Z: CMP1.P$6 (OUT_5)
R2_IS_N: CMP1.P$3 (OUT_2)
R2_IS_Z: CMP1.P$7 (OUT_6)
R3_IS_N: CMP1.P$4 (OUT_3)
R3_IS_Z: CMP1.P$8 (OUT_7)
STATE_0: CMP12.P$1 (OUT_0); also elsewhere on the board
STATE_1: CMP12.P$2 (OUT_1); also elsewhere on the board
STATE_2: CMP12.P$3 (OUT_2); also elsewhere on the board
STATE_3: CMP12.P$4 (OUT_3); also elsewhere on the board
STATE_4: CMP12.P$5 (OUT_4)
STATE_5: CMP12.P$6 (OUT_5)
STATE_6: CMP12.P$7 (OUT_6); also elsewhere on the board
STATE_7: CMP12.P$8 (OUT_7); also elsewhere on the board
STATE_8: CMP12.P$9 (OUT_8)
STATE_9: CMP12.P$10 (OUT_9)
STATE_10: CMP12.P$11 (OUT_10); also elsewhere on the board
STATE_11: CMP12.P$12 (OUT_11); also elsewhere on the board
STATE_12: CMP12.P$13 (OUT_12); also elsewhere on the board
STATE_13: CMP12.P$14 (OUT_13); also elsewhere on the board
STATE_14: CMP12.P$15 (OUT_14); also elsewhere on the board
STATE_15: CMP12.P$16 (OUT_15); also elsewhere on the board

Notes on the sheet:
clBit add2_x_mux_ri__h; // 0 clBit add2_x_mux_ri__sp__jsr_abs; // 1 clBit add2_x_mux_ri__sp; // 2 clBit next_addr_mux_ri__sp; // 3 clBit adder_x_special; // 4 clBit adder_y_special; // 5
